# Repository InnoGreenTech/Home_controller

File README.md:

# Home_controller
Home controller allow to pilote the VMC.  For this it reads the CO2, Humidity and temperature. It is able also forecast the Weather. It have a touch screen.

Description:
------------

Home controller allow to pilote a VMC. It use a MH-Z19B sensor to measure the C02 and DHT22 for humidity and temperature in the pipe of the ventilation.
A BME280 allow to measure humidity, temperature and pressure in out door, like this is possible to forecaste weather.

There are a main card with a touch screen and a remote VMC.

Also ther is another modul to measure the power consomation of the house. Is it possible to read them in real time.

A optional ESP8266, allow to sent data with a Json file and it is possible to connect at a webpage with evry information.

[*You can found more information on my web site on this page*](https://innogreentech.fr/fr/objets-connectes/mesures/70-controleur-de-vmc)

I share also the drawing, the pcb, and the box designe in this repository.

Screen interface:
----------------

Remote VMC:
----------------

Remote energie meter:
----------------

Contributing:
-------------

Fork it.
Create your feature branch (git checkout -b my-new-feature).
Commit your changes (git commit -am 'Add some feature').
Push to the branch (git push origin my-new-feature).
Create new Pull Request.

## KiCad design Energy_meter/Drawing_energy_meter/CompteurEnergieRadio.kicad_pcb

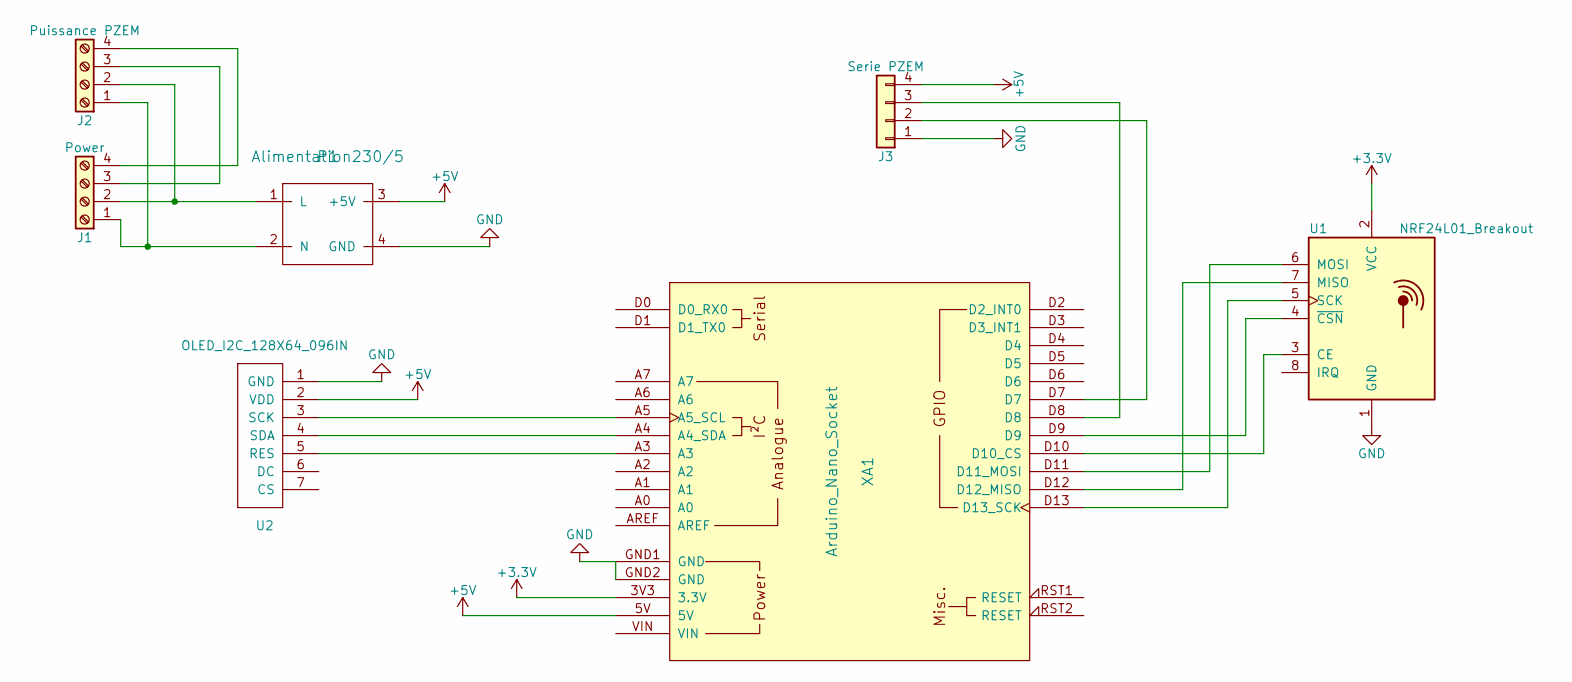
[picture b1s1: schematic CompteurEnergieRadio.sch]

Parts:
J1: Power; TerminalBlock_bornier-4_P5.08mm
J2: Puissance PZEM; TerminalBlock_bornier-4_P5.08mm
J3: Serie PZEM; JST_EH_B04B-EH-A_04x2.50mm_Straight
P1: Alimentation230/5; Alimentation5V
U1: NRF24L01_Breakout; nRF24L01_Breakout
U2: OLED_I2C_128X64_096IN; 96OLEDV2
XA1: Arduino_Nano_Socket; Arduino_Nano_2

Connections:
+3V3: U1.2 (VCC), XA1.3V3 (3.3V)
+5V: J3.4, P1.3 (+5V), U2.2 (VDD), XA1.5V
GND: J3.1, P1.4 (GND), U1.1 (GND), U2.1 (GND), XA1.GND1 (GND), XA1.GND2 (GND)
unnamed: J1.1, J2.1, P1.2 (N)
unnamed: J1.2, J2.2, P1.1 (L)
unnamed: J1.3, J2.3
unnamed: J1.4, J2.4
unnamed: J3.2, XA1.D7
unnamed: J3.3, XA1.D8
unnamed: U1.3 (CE), XA1.D10 (D10_CS)
unnamed: U1.4 (~CSN), XA1.D9
unnamed: U1.5 (SCK), XA1.D13 (D13_SCK)
unnamed: U1.6 (MOSI), XA1.D11 (D11_MOSI)
unnamed: U1.7 (MISO), XA1.D12 (D12_MISO)
unnamed: U2.3 (SCK), XA1.A5 (A5_SCL)
unnamed: U2.4 (SDA), XA1.A4 (A4_SDA)
unnamed: U2.5 (RES), XA1.A3

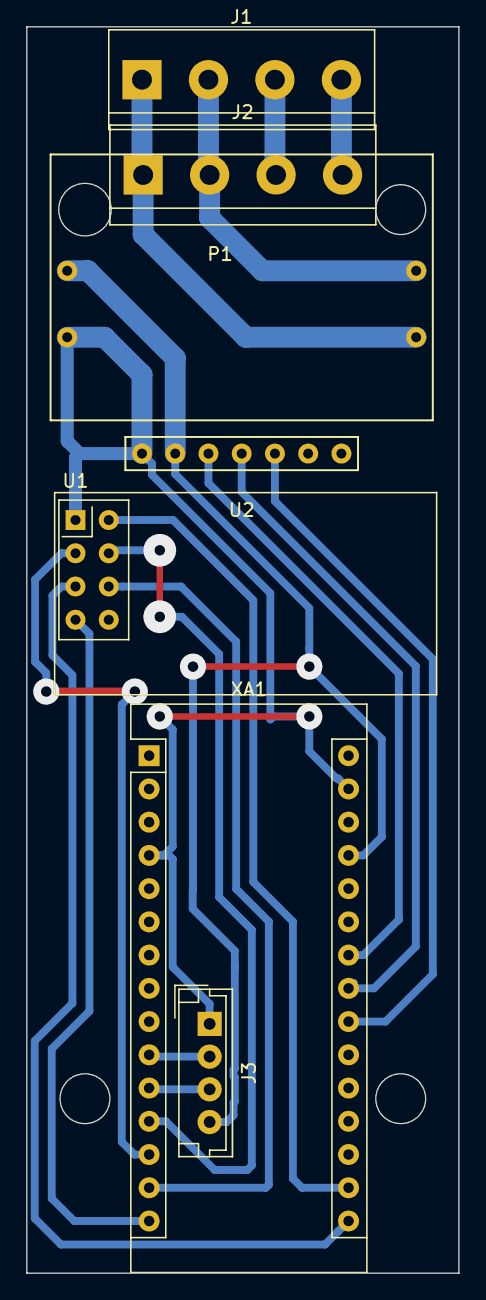
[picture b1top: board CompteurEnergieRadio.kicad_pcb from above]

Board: 2 copper layers, 33.0 x 95.3 mm, 7 parts (0 on the bottom side), 17 nets.

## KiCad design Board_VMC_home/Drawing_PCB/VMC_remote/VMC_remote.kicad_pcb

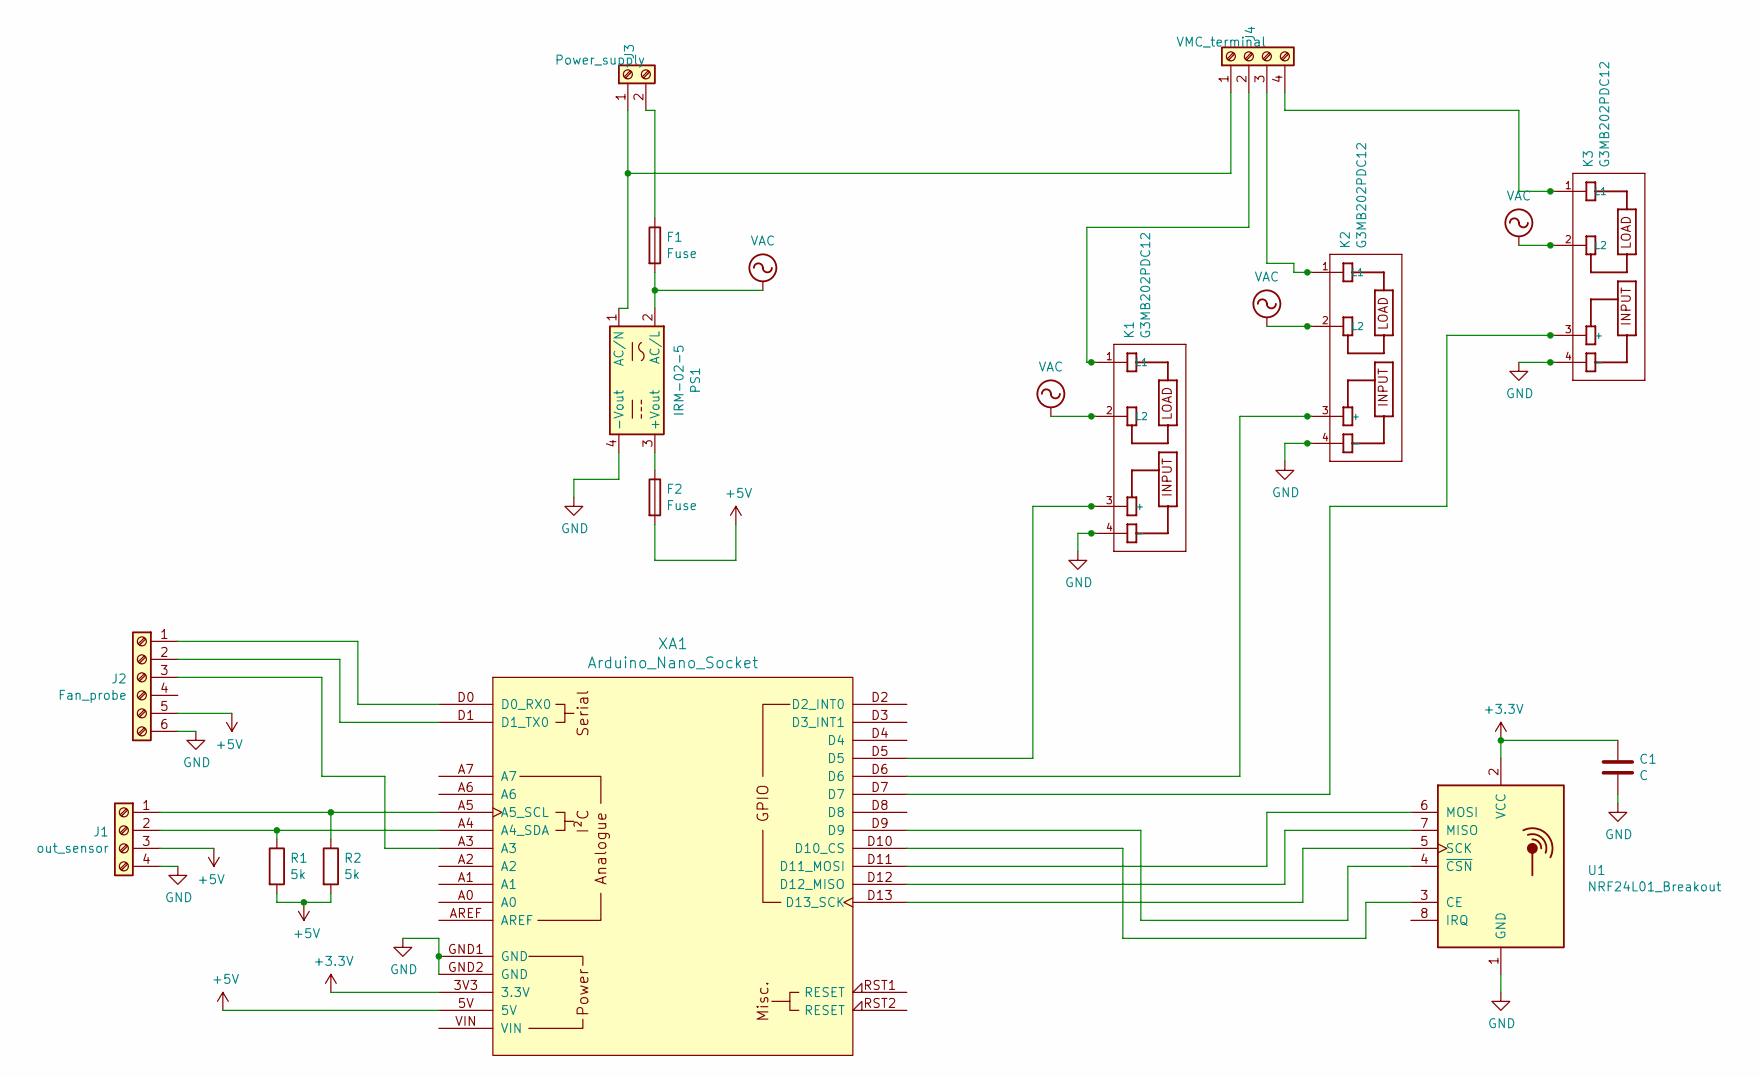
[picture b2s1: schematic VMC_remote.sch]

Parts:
C1: C; C_Disc_D7.0mm_W2.5mm_P5.00mm
F1, F2: Fuse; R_Axial_DIN0516_L15.5mm_D5.0mm_P20.32mm_Horizontal
J1: out_sensor; TerminalBlock_4Ucon_1x04_P3.50mm_Horizontal
J2: Fan_probe; TerminalBlock_4Ucon_1x06_P3.50mm_Horizontal
J3: Power_supply; TerminalBlock_bornier-2_P5.08mm
J4: VMC_terminal; TerminalBlock_bornier-4_P5.08mm
K1, K2, K3: G3MB202PDC12; RELAY_G3MB202PDC12
PS1: IRM-02-5; Converter_ACDC_MeanWell_IRM-02-xx_THT
R1, R2: 5k; R_Axial_DIN0411_L9.9mm_D3.6mm_P12.70mm_Horizontal
U1: NRF24L01_Breakout; nRF24L01_Breakout
XA1: Arduino_Nano_Socket

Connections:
+3V3: C1.1, U1.2 (VCC), XA1.3V3 (3.3V)
+5V: F2.2, J1.3, J2.5, R1.2, R2.2, XA1.5V
GND: C1.2, J1.4, J2.6, K1.4 (-), K2.4 (-), K3.4 (-), PS1.4 (-Vout), U1.1 (GND), XA1.GND1 (GND), XA1.GND2 (GND)
unnamed: F1.1, J3.2
unnamed: F2.1, PS1.3 (+Vout)
unnamed: J1.1, R2.1, XA1.A5 (A5_SCL)
unnamed: J1.2, R1.1, XA1.A4 (A4_SDA)
unnamed: J2.1, XA1.D0 (D0_RX0)
unnamed: J2.2, XA1.D1 (D1_TX0)
unnamed: J2.3, XA1.A3
unnamed: J3.1, J4.1, PS1.1 (AC/N)
unnamed: J4.2, K1.1 (L1)
unnamed: J4.3, K2.1 (L1)
unnamed: J4.4, K3.1 (L1)
unnamed: K1.3 (+), XA1.D5
unnamed: K2.3 (+), XA1.D6
unnamed: K3.3 (+), XA1.D7
unnamed: U1.3 (CE), XA1.D10 (D10_CS)
unnamed: U1.4 (~CSN), XA1.D9
unnamed: U1.5 (SCK), XA1.D13 (D13_SCK)
unnamed: U1.6 (MOSI), XA1.D11 (D11_MOSI)
unnamed: U1.7 (MISO), XA1.D12 (D12_MISO)
VAC: F1.2, K1.2 (L2), K2.2 (L2), K3.2 (L2), PS1.2 (AC/L)

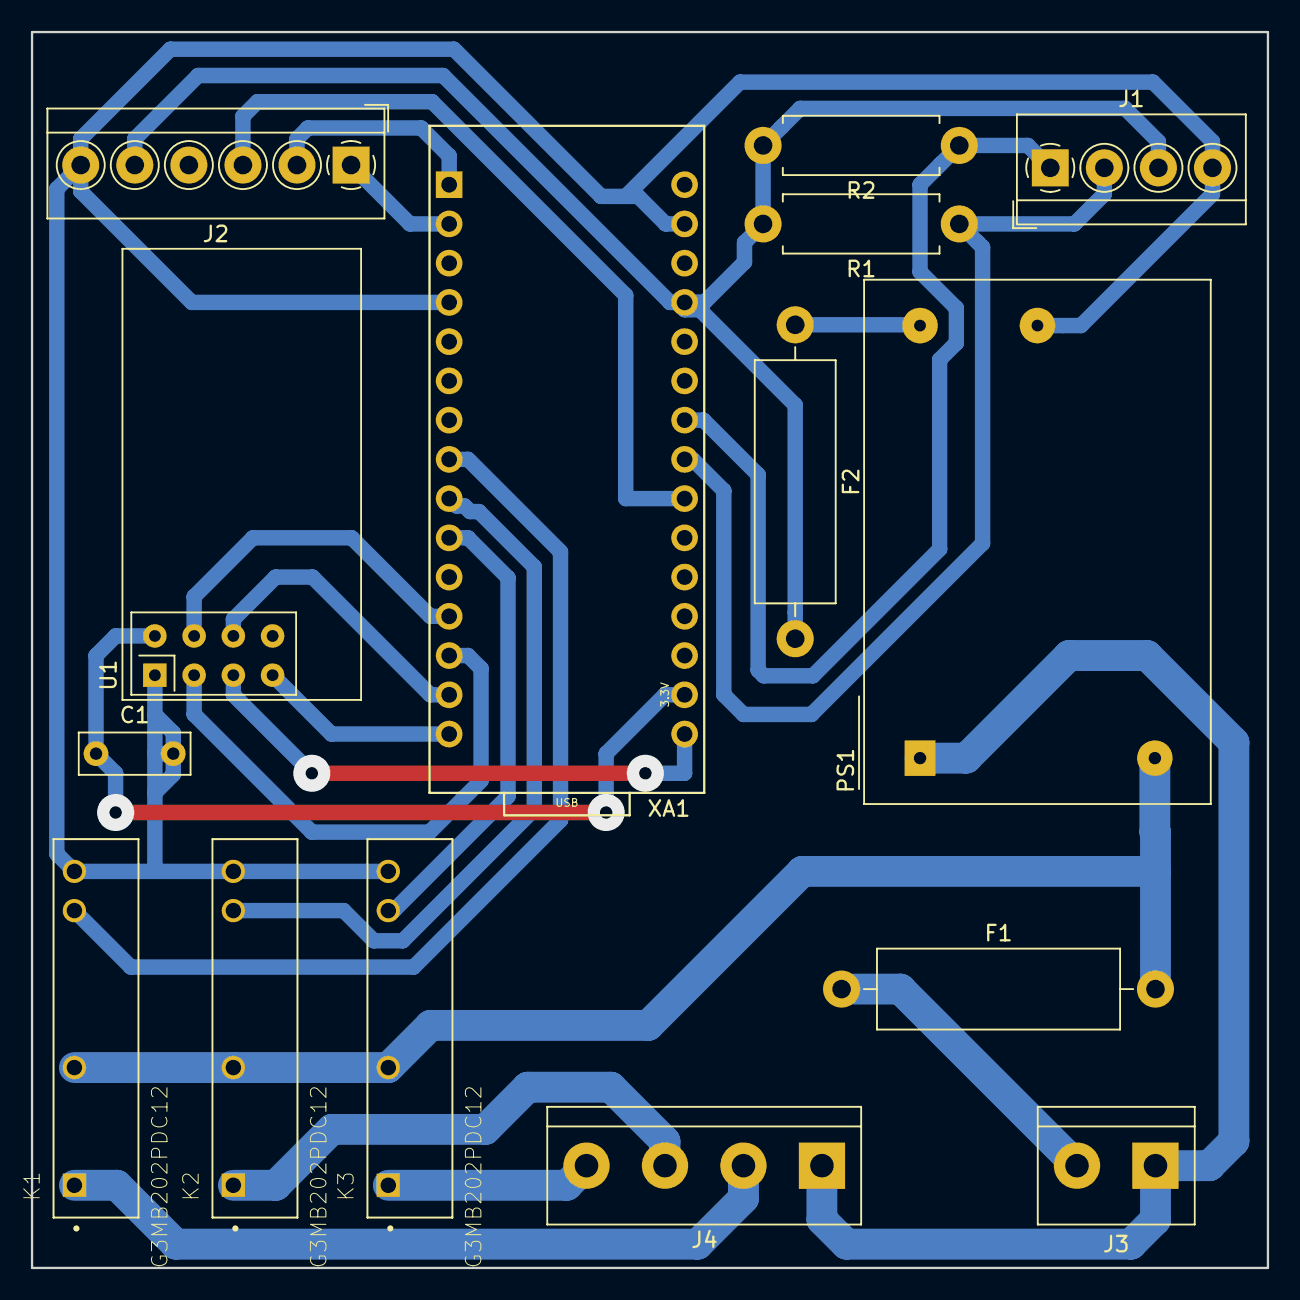
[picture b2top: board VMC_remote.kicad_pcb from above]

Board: 2 copper layers, 80.0 x 80.0 mm, 15 parts (0 on the bottom side), 23 nets.

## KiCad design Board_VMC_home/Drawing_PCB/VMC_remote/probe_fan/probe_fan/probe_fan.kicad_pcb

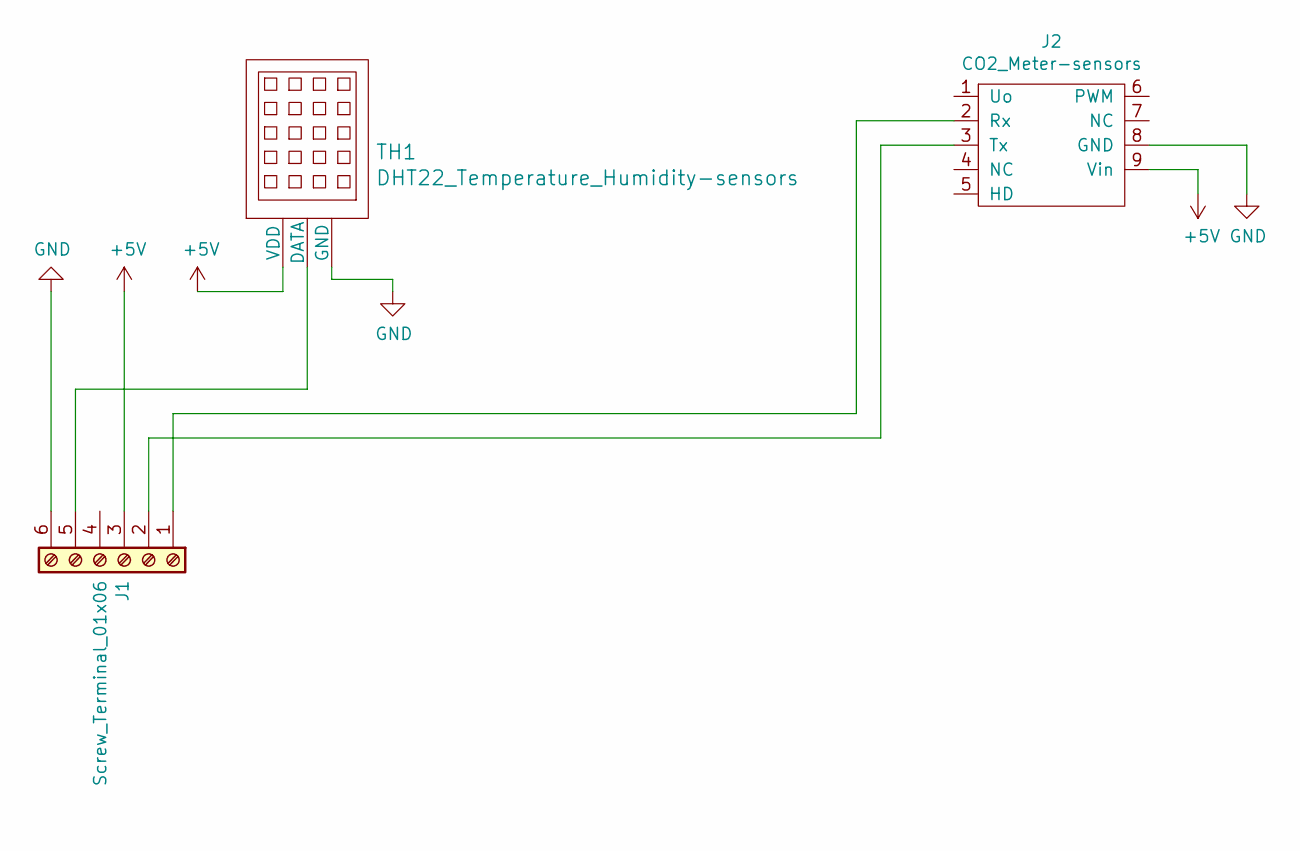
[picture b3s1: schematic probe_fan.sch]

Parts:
J1: Screw_Terminal_01x06; TerminalBlock_MetzConnect_Type059_RT06306HBWC_1x06_P3.50mm_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
J2: CO2_Meter-sensors; MHZ19B
TH1: DHT22_Temperature_Humidity-sensors; DHT22_Temperature_Humidity

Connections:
+5V: J1.3, J2.9 (Vin), TH1.1 (VDD)
GND: J1.6, J2.8 (GND), TH1.3 (GND)
unnamed: J1.1, J2.2 (Rx)
unnamed: J1.2, J2.3 (Tx)
unnamed: J1.5, TH1.2 (DATA)

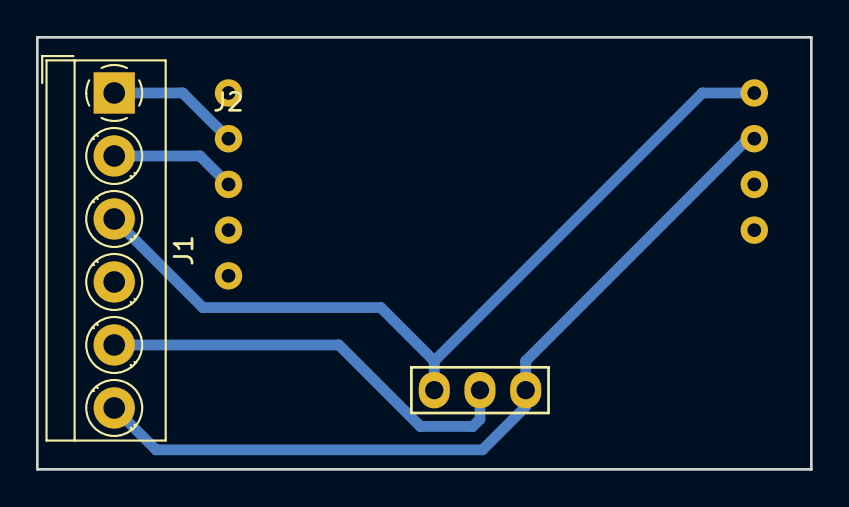
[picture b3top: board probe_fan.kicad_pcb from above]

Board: 2 copper layers, 43.0 x 24.0 mm, 3 parts (0 on the bottom side), 5 nets.

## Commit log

2020-05-04 weather correction
2020-05-04 improve weather forecast
2020-05-05 fix bog forecast
2020-06-08 Update vmc board
2020-06-08 add new file
2020-07-11 Update little correctif
2020-11-20 update for screen
2020-11-21 add cnc files
2020-12-22 Correction on PCB and add cover stl file
2020-12-22 add new file for pcb
2021-01-10 update PZEM V3
2021-02-06 add documentation to extend I2C bus
